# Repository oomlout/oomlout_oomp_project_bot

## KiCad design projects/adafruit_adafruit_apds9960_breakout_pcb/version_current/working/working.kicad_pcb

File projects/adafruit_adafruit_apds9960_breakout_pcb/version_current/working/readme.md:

# Adafruit-APDS9960-Breakout-PCB by adafruit  
This is a harvested standardized copy of a project from github.  
The original project can be found at:  
https://github.com/adafruit/Adafruit-APDS9960-Breakout-PCB  
Please consult that link for additional, details, files, and license information.  
Note: It was auto harvested and if the original repo had more than one board file or anything out of the ordinary the files here are likely not representative.

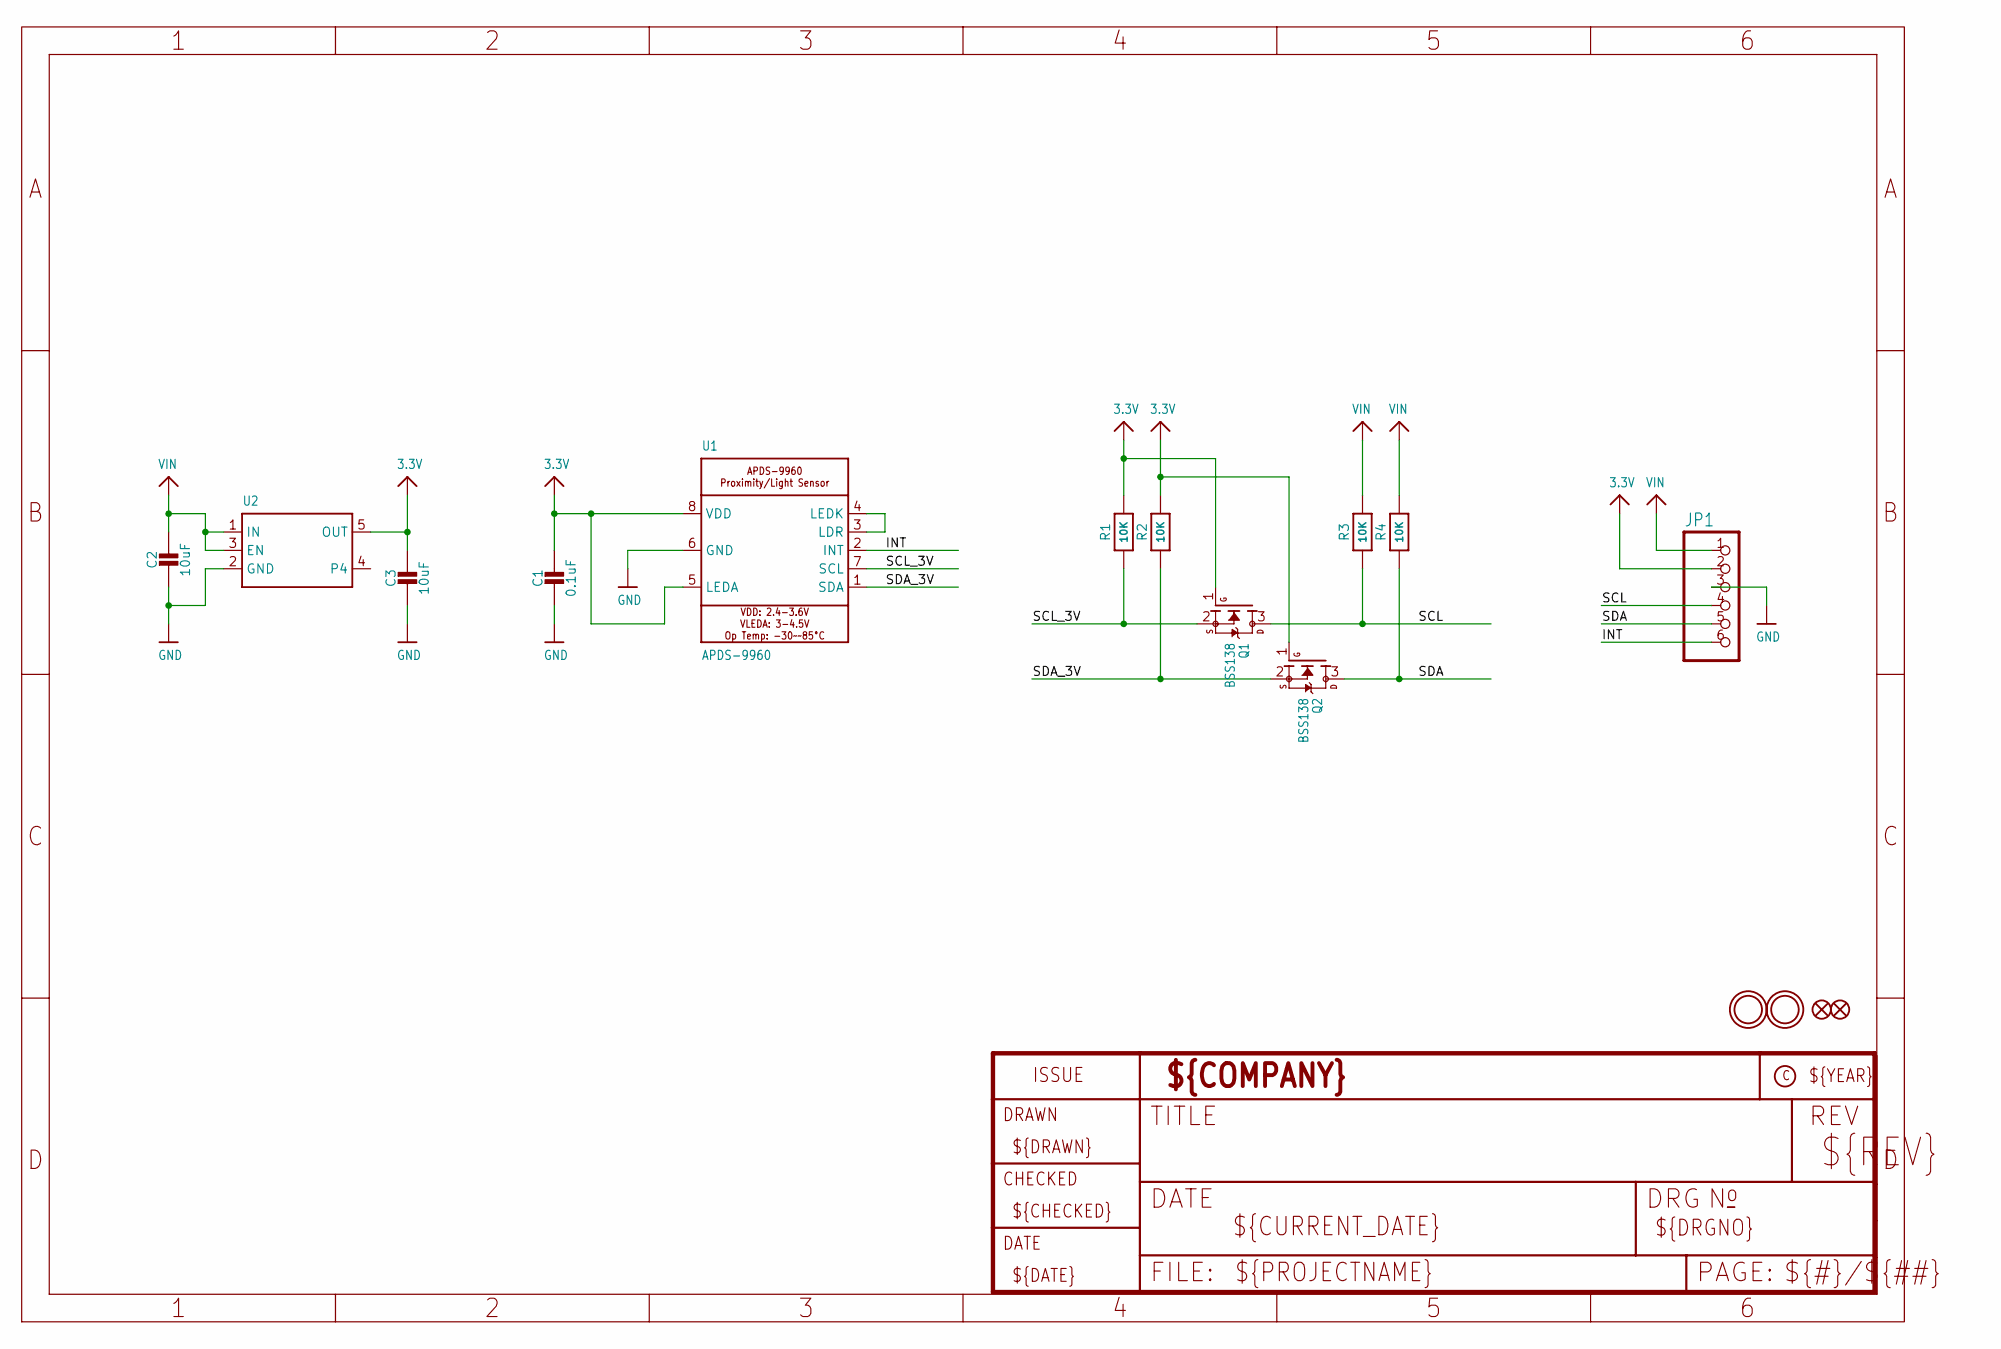
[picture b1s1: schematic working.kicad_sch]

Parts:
C1: 0.1uF; 0805-NO
C2, C3: 10uF; 0805-NO
FID1, FID2: FIDUCIAL_1MM
JP1: HEADER-1X676MIL; 1X06_ROUND_76
Q1, Q2: BSS138; SOT23-WIDE
R1, R2, R3, R4: 10K; 0805-NO
U1: APDS-9960
U2: VREG_SOT23-5; SOT23-5
U$1, U$2: MOUNTINGHOLE2.5; MOUNTINGHOLE_2.5_PLATED

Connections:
3.3V: C1.1, C3.1, JP1.2, Q1.1 (G), Q2.1 (G), R1.2, R2.2, U1.5 (LEDA), U1.8 (VDD), U2.5 (OUT)
GND: C1.2, C2.2, C3.2, JP1.3, U1.6 (GND), U2.2 (GND)
INT: JP1.6, U1.2 (INT)
unnamed: U1.3 (LDR), U1.4 (LEDK)
SCL: JP1.4, Q1.3 (D), R3.1
SCL_3V: Q1.2 (S), R1.1, U1.7 (SCL)
SDA: JP1.5, Q2.3 (D), R4.1
SDA_3V: Q2.2 (S), R2.1, U1.1 (SDA)
VIN: C2.1, JP1.1, R3.2, R4.2, U2.1 (IN), U2.3 (EN)

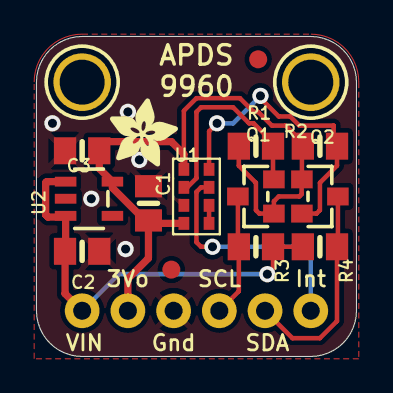
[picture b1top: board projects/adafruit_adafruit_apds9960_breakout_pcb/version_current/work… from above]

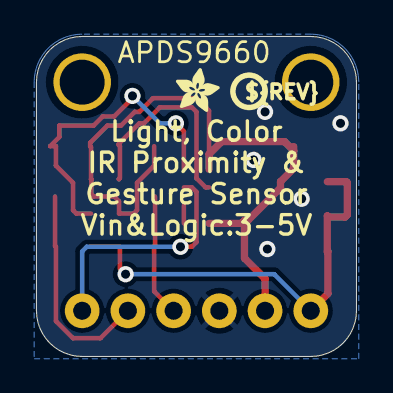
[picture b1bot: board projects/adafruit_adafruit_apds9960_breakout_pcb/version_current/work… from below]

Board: 2 copper layers, 17.8 x 17.8 mm, 19 parts (2 on the bottom side), 9 nets.

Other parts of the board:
U$17: PCBFEAT-REV-040
U$18: ADAFRUIT_2.5MM
U$19: ADAFRUIT_3.5MM

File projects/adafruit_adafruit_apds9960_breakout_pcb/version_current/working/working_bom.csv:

Row,Description,Part,References,Value,Footprint,Quantity Per PCB,Status,Datasheet
1,,CAP_CERAMIC0805-NOOUTLINE,C1,0.1uF,0805-NO,1, ,
2,,CAP_CERAMIC0805-NOOUTLINE,C2 C3,10uF,0805-NO,2, ,
3,,HEADER-1X676MIL,JP1,HEADER-1X676MIL,1X06_ROUND_76,1, ,
4,,MOSFET-NWIDE,Q1 Q2,BSS138,SOT23-WIDE,2, ,
5,,RESISTOR0805_NOOUTLINE,R1 R2 R3 R4,10K,0805-NO,4, ,
6,,APDS-9960,U1,APDS-9960,APDS-9960,1, ,
7,,VREG_SOT23-5,U2,VREG_SOT23-5,SOT23-5,1, ,





Project info:
Schematic:,working
Variant:,default
Revision:,
Date:,2023-08-02_17-08-32
KiCad Version:,7.0.6-7.0.6~ubuntu22.04.1
Statistics:
Component Groups:,7
Component Count:,12 (0 SMD/ 0 THT)
Fitted Components:,12 (0 SMD/ 0 THT)
Number of PCBs:,1
Total Components:,12

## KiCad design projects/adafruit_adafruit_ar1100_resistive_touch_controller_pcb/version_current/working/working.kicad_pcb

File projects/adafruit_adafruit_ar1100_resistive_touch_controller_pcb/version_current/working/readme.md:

# Adafruit-AR1100-Resistive-Touch-Controller-PCB by adafruit  
This is a harvested standardized copy of a project from github.  
The original project can be found at:  
https://github.com/adafruit/Adafruit-AR1100-Resistive-Touch-Controller-PCB  
Please consult that link for additional, details, files, and license information.  
Note: It was auto harvested and if the original repo had more than one board file or anything out of the ordinary the files here are likely not representative.

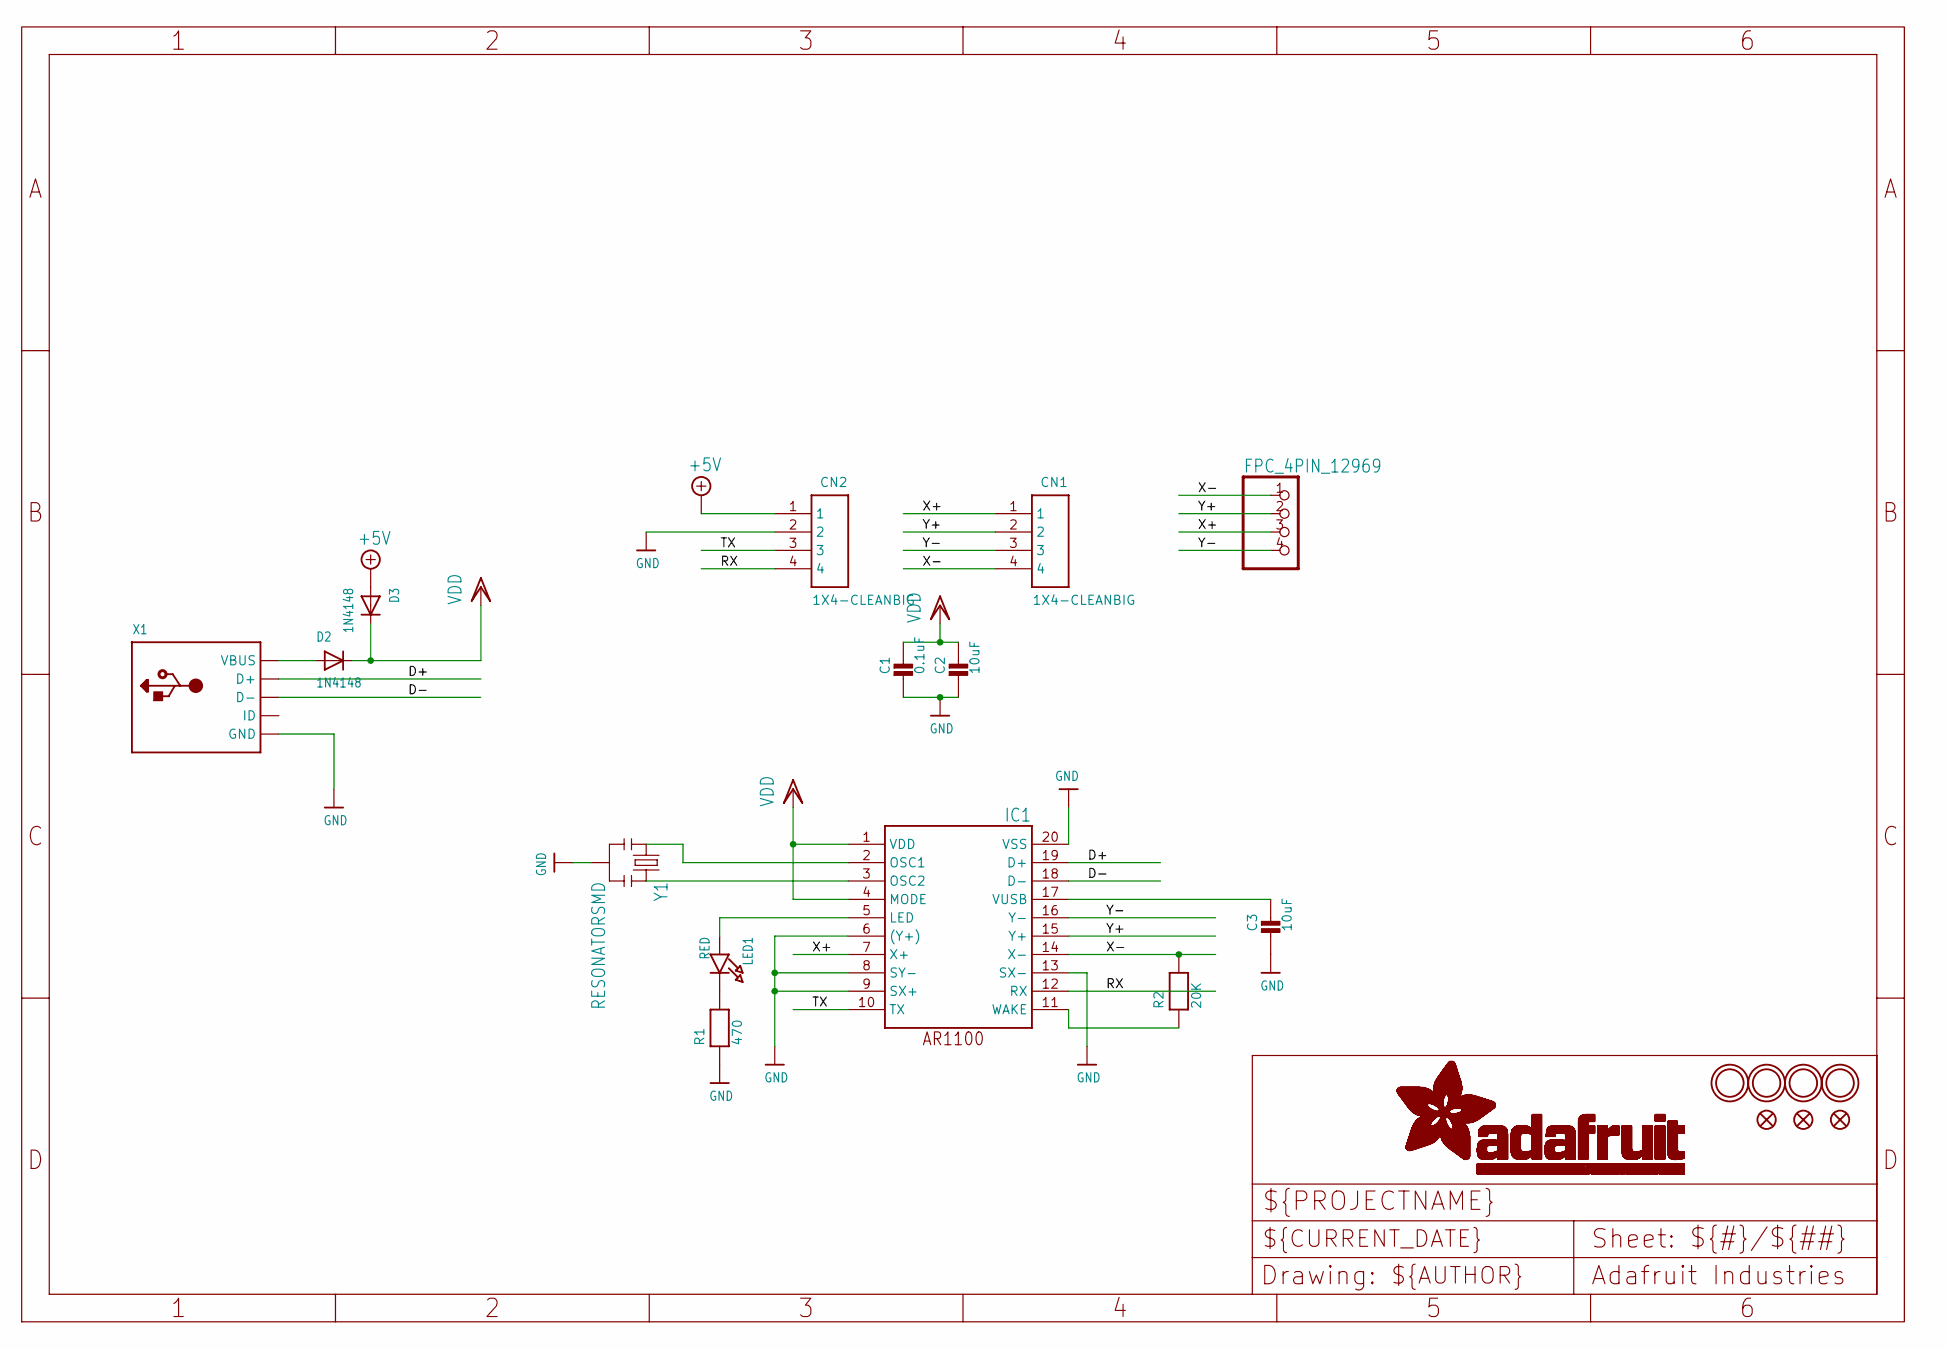
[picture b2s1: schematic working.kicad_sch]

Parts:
C1: 0.1uF; 0805-NO
C2, C3: 10uF; 0805-NO
CN1, CN2: 1X4-CLEANBIG; 1X04-CLEANBIG
D2, D3: 1N4148; SOD-323F
FID1, FID2, FID3: FIDUCIAL""; FIDUCIAL_1MM
IC1: AR1100_SSOP; TSSOP20-5.3MMBODY
LED1: RED; CHIPLED_0805_NOOUTLINE
R1: 470; 0805-NO
R2: 20K; 0805-NO
U$2, U$4, U$5, U$6: MOUNTINGHOLE2.5; MOUNTINGHOLE_2.5_PLATED
U$7: FPC_4PIN_12969; FPC_CONN_1MM_DUAL_4P
X1: USBMINIB; USB-MINIB
Y1: RESONATORSMD; RESONATOR-SMD

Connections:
+5V: CN2.1, D3.A
D+: IC1.19 (D+), X1.D+
D-: IC1.18 (D-), X1.D-
GND: C1.2, C2.2, C3.2, CN2.2, IC1.6 ((Y+)), IC1.8 (SY-), IC1.9 (SX+), IC1.13 (SX-), IC1.20 (VSS), R1.1, X1.GND, X1.GND1 (GND), X1.GND2 (GND), X1.GND3 (GND), X1.GND4 (GND), Y1.2
unnamed: D2.A, X1.VBUS
unnamed: IC1.5 (LED), LED1.A
unnamed: LED1.C, R1.2
unnamed: C3.1, IC1.17 (VUSB)
unnamed: IC1.11 (WAKE), R2.1
unnamed: IC1.3 (OSC2), Y1.3
unnamed: IC1.2 (OSC1), Y1.1
RX: CN2.4, IC1.12 (RX)
TX: CN2.3, IC1.10 (TX)
VDD: C1.1, C2.1, D2.C, D3.C, IC1.1 (VDD), IC1.4 (MODE)
X+: CN1.1, IC1.7 (X+), U$7.3 (2)
X-: CN1.4, IC1.14 (X-), R2.2, U$7.1 (4)
Y+: CN1.2, IC1.15 (Y+), U$7.2 (3)
Y-: CN1.3, IC1.16 (Y-), U$7.4 (1)

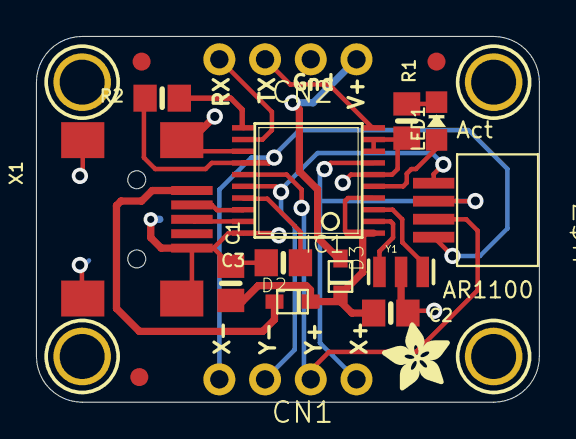
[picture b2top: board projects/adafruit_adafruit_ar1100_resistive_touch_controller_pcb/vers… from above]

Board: 2 copper layers, 27.9 x 20.3 mm, 23 parts (1 on the bottom side), 18 nets.

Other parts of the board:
U$14: ADAFRUIT_3.5MM
U$17: ADAFRUIT_TEXT_20MM

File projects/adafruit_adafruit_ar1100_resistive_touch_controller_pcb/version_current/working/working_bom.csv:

Row,Description,Part,References,Value,Footprint,Quantity Per PCB,Status,Datasheet,BOM
1,,CAP_CERAMIC0805-NOOUTLINE,C1,0.1uF,0805-NO,1, ,,
2,,CAP_CERAMIC0805-NOOUTLINE,C2 C3,10uF,0805-NO,2, ,,
3,,1X4-CLEANBIG,CN1 CN2,1X4-CLEANBIG,1X04-CLEANBIG,2, ,,
4,,DIODESOD-323F,D2 D3,1N4148,SOD-323F,2, ,,
5,,AR1100_SSOP,IC1,AR1100_SSOP,TSSOP20-5.3MMBODY,1, ,,
6,,LED0805_NOOUTLINE,LED1,RED,CHIPLED_0805_NOOUTLINE,1, ,,
7,,RESISTOR0805_NOOUTLINE,R1,470,0805-NO,1, ,,
8,,RESISTOR0805_NOOUTLINE,R2,20K,0805-NO,1, ,,
9,,FPC_4PIN_12969,U$7,FPC_4PIN_12969,FPC_CONN_1MM_DUAL_4P,1, ,,
10,,USBMINIB,X1,USBMINIB,USB-MINIB,1, ,,
11,,RESONATORSMD,Y1,RESONATORSMD,RESONATOR-SMD,1, ,,





Project info:
Schematic:,working
Variant:,default
Revision:,
Date:,2023-08-02_17-08-32
KiCad Version:,7.0.6-7.0.6~ubuntu22.04.1
Statistics:
Component Groups:,11
Component Count:,14 (0 SMD/ 0 THT)
Fitted Components:,14 (0 SMD/ 0 THT)
Number of PCBs:,1
Total Components:,14

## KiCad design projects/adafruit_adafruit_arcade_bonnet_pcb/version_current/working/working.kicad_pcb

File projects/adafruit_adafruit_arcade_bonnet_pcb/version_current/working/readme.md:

# OOMP Project  
## Adafruit-Arcade-Bonnet-PCB  by adafruit  
  
oomp key: oomp_projects_flat_adafruit_adafruit_arcade_bonnet_pcb  
(snippet of original readme)  
  
-- Adafruit Arcade Bonnet PCB  
  
<a href="http://www.adafruit.com/products/3422"><br/>  
Click here to purchase one from the Adafruit shop</a>  
  
PCB files for the Adafruit Arcade Bonnet. Format is EagleCAD schematic and board layout  
* http://www.adafruit.com/product/3422  
  
--- Description  
  
Playing retro games is easy on a Raspberry Pi - and that pocket-sized computer is pretty good at it too! All you need is a little help to connect buttons and a joystick up and you can custom design your own arcade console, desktop or stand-up machine, even just a simple controller box. It makes for a fun weekend project that will last all year.  
  
This Adafruit Arcade Bonnet is designed to make small emulator projects a little easier to build. Here's what you can look forward to!  
  
* It is the same size as a Pi Zero, so for really compact builds, this is super small. You can also use it with a Pi 2, 3, B+ or any 2x20 connector Pi.  
* It has JST sockets so you can plug in six arcade buttons easily using our quick connects.  
* Header breakouts for use with both clicky-type switched joysticks and...  
* Header breakout and converter for using analog-type joysticks or thumbsticks with potentiometers inside.  
* A 3W digital speaker output that can drive 4-8 ohm speakers for when using with a TV output, audio-less HDMI display or PiTFT. Works even when the Pi doesn't have a headphone jack!  
* Switches are all managed with an I2C-GPIO converter with interrupt ou  
  full source readme at [readme_src.md](readme_src.md)  
  
source repo at: [https://github.com/adafruit/Adafruit-Arcade-Bonnet-PCB](https://github.com/adafruit/Adafruit-Arcade-Bonnet-PCB)  
## Board  

## Schematic  

[schematic pdf](working_schematic.pdf)  
## Images

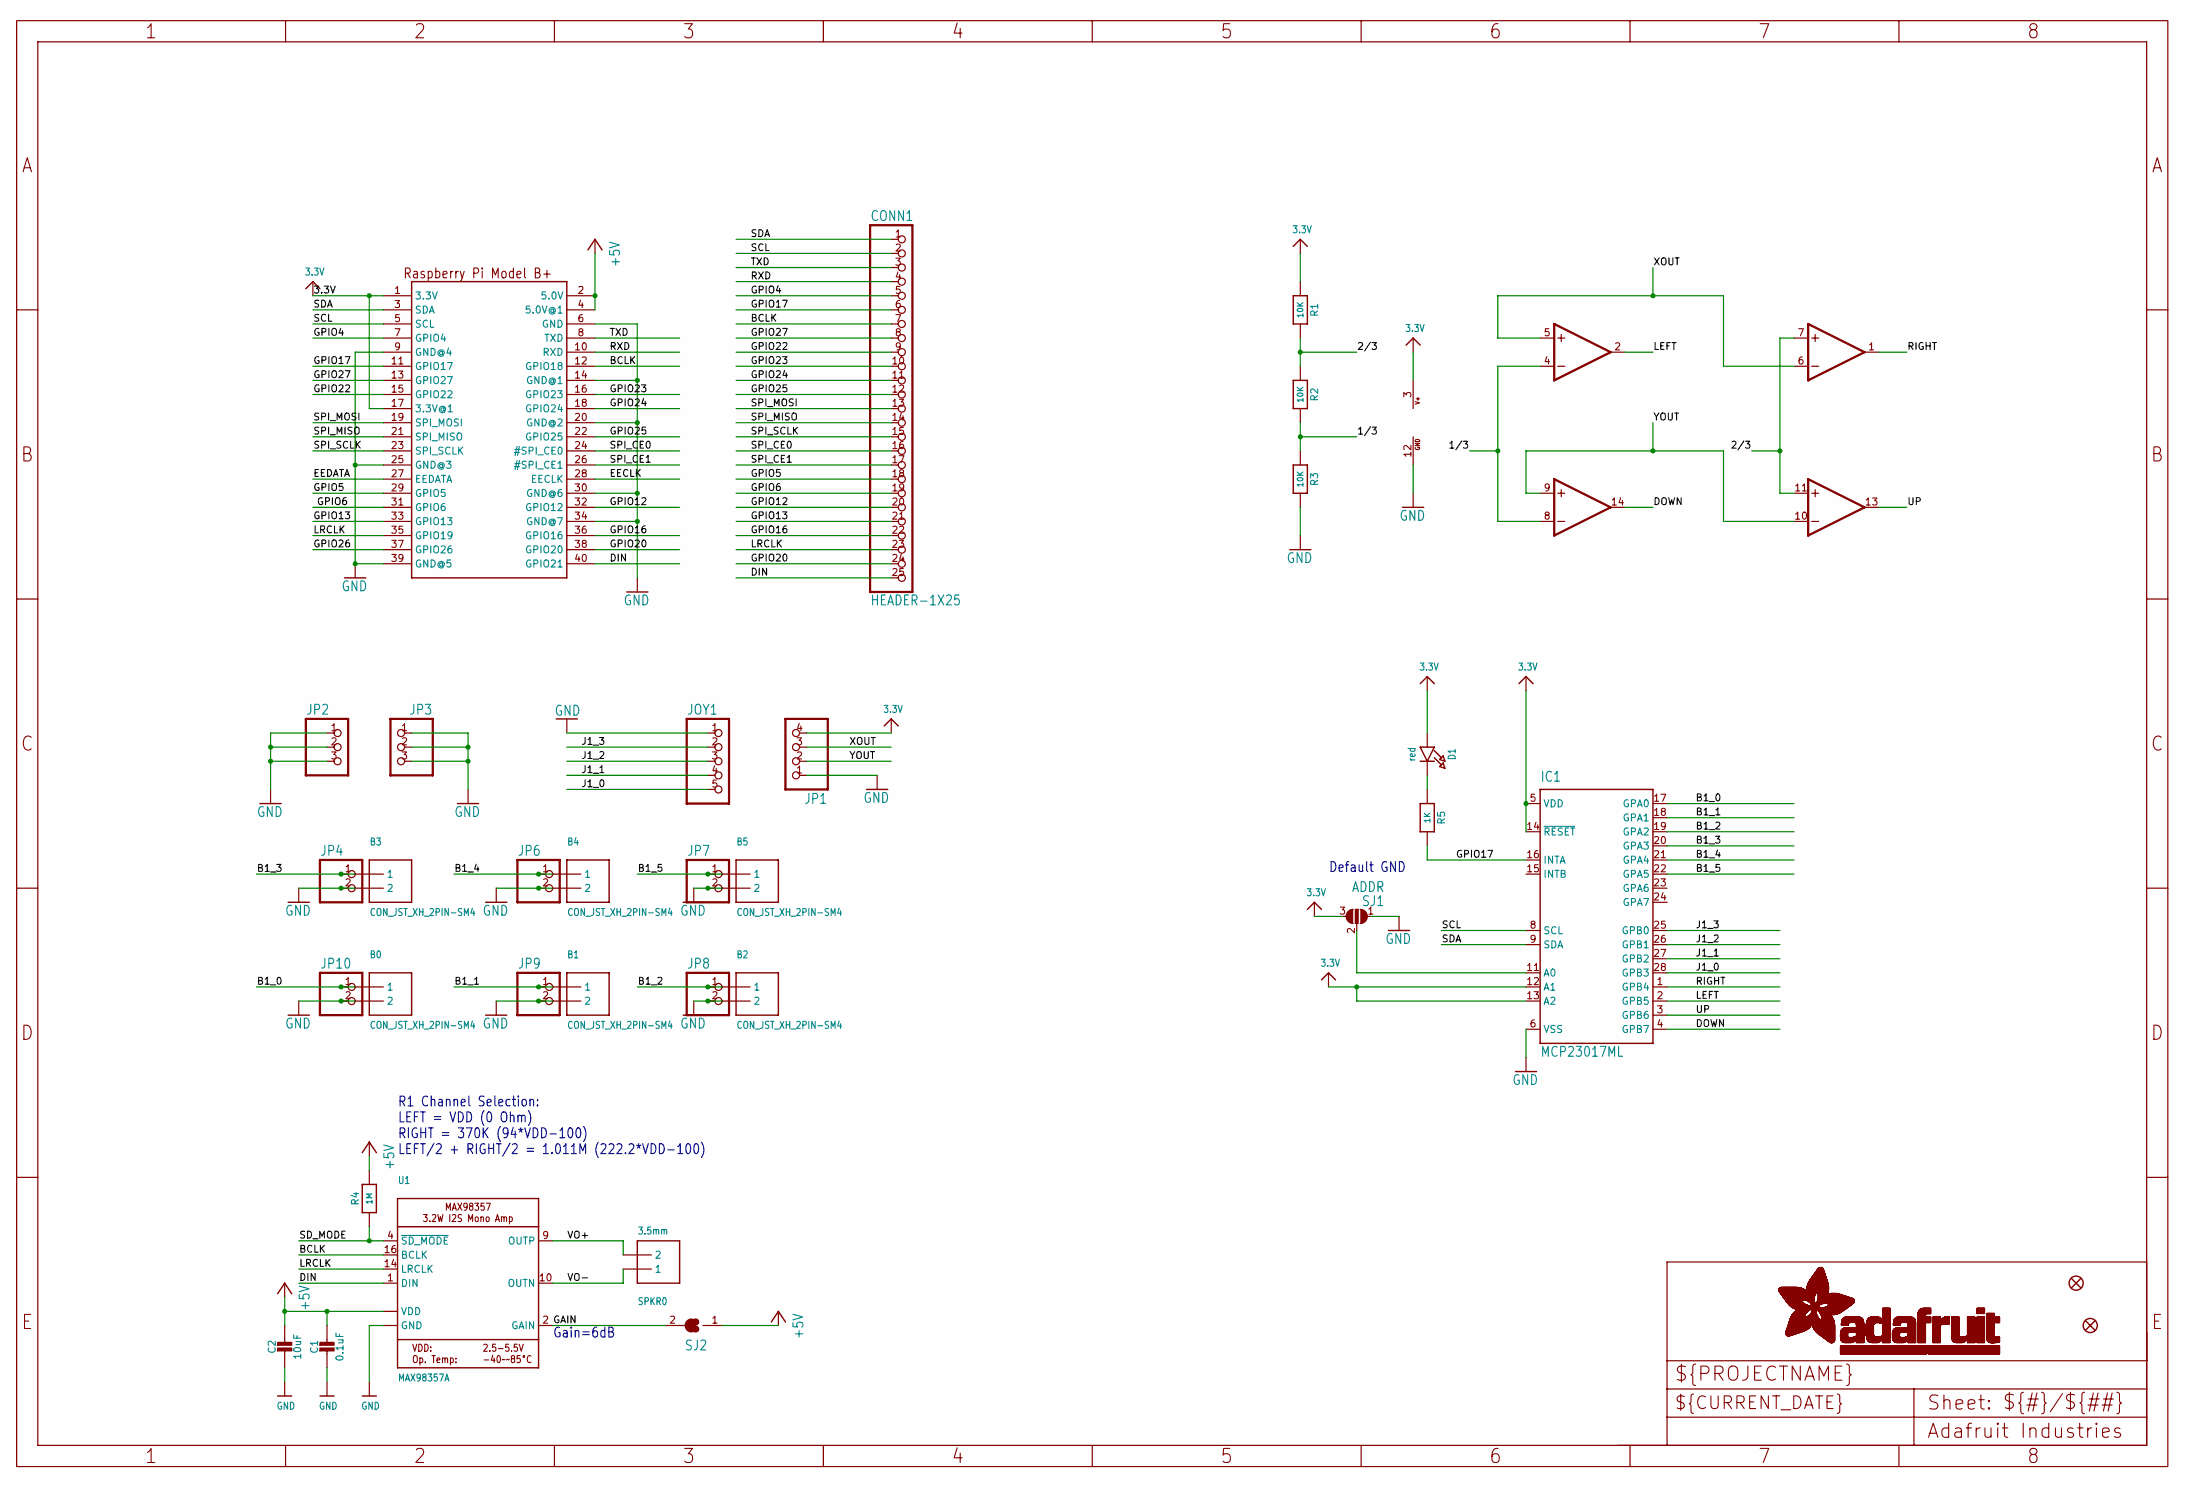
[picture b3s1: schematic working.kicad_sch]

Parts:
B0, B1, B2, B3, B4, B5: CON_JST_XH_2PIN-SM4; JST-XH-2-SM4
C1: 0.1uF; 0603-NO
C2: 10uF; 0805-NO
CONN1: HEADER-1X25; 1X25_ROUND_70MIL
D1: red; CHIPLED_0805_NOOUTLINE
FID2, FID3: FIDUCIAL""; FIDUCIAL_1MM
IC1: MCP23017ML; QFN28-ML_6X6MM; MPN MCP23017-E/SS
IC2: LM339P; TSSOP14
JOY1: HEADER-1X5; 1X05_OVAL
JP1: HEADER-1X4; 1X04_OVAL
JP2, JP3: HEADER-1X3ROUND; 1X03_ROUND
JP4, JP6, JP7, JP8, JP9, JP10: HEADER-1X2; 1X02_OVAL
R1: 10K; 0805_10MGAP
R2, R3: 10K; 0805-NO
R4: 1M; 0603-NO
R5: 1K; 0603-NO
RPI1: RASPBERRYPI_BPLUS_PHAT; PI_BONNET
SJ1: ADDR; SOLDERJUMPER_2WAY_OPEN_NOPASTE
SJ2: SOLDERJUMPERCLOSED; SOLDERJUMPER_CLOSEDWIRE
SPKR0: 3.5mm; TERMBLOCK_1X2-3.5MM
U1: MAX98357A; QFN16_3MM

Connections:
1/3: IC2.4 (-IN), IC2.8 (-IN), R2.2, R3.1
2/3: IC2.7 (+IN), IC2.11 (+IN), R1.2, R2.1
3.3V: D1.A, IC1.5 (VDD), IC1.12 (A1), IC1.13 (A2), IC1.14 (~RESET), IC2.3 (V+), JP1.4, R1.1, RPI1.1 (3.3V), RPI1.17 (3.3V@1), SJ1.3
+5V: C1.1, C2.1, R4.2, RPI1.2 (5.0V), RPI1.4 (5.0V@1), SJ2.1, U1.7 (VDD), U1.8 (VDD)
B1_0: B0.1, IC1.17 (GPA0), JP10.1
B1_1: B1.1, IC1.18 (GPA1), JP9.1
B1_2: B2.1, IC1.19 (GPA2), JP8.1
B1_3: B3.1, IC1.20 (GPA3), JP4.1
B1_4: B4.1, IC1.21 (GPA4), JP6.1
B1_5: B5.1, IC1.22 (GPA5), JP7.1
BCLK: CONN1.7, RPI1.12 (GPIO18), U1.16 (BCLK)
DIN: CONN1.25, RPI1.40 (GPIO21), U1.1 (DIN)
DOWN: IC1.4 (GPB7), IC2.14 (OUT)
EECLK: RPI1.28 (EECLK)
EEDATA: RPI1.27 (EEDATA)
GAIN: SJ2.2, U1.2 (GAIN)
GND: B0.2, B1.2, B2.2, B3.2, B4.2, B5.2, C1.2, C2.2, IC1.6 (VSS), IC2.12 (GND), JOY1.1, JP1.1, JP2.1, JP2.2, JP2.3, JP3.1, JP3.2, JP3.3, JP4.2, JP6.2, JP7.2, JP8.2, JP9.2, JP10.2, R3.2, RPI1.6 (GND), RPI1.9 (GND@4), RPI1.14 (GND@1), RPI1.20 (GND@2), RPI1.25 (GND@3), RPI1.30 (GND@6), RPI1.34 (GND@7), RPI1.39 (GND@5), SJ1.1, U1.3 (GND), U1.11 (GND), U1.15 (GND), U1.THERMAL (GND)
GPIO4: CONN1.5, RPI1.7 (GPIO4)
GPIO5: CONN1.18, RPI1.29 (GPIO5)
GPIO6: CONN1.19, RPI1.31 (GPIO6)
GPIO12: CONN1.20, RPI1.32 (GPIO12)
GPIO13: CONN1.21, RPI1.33 (GPIO13)
GPIO16: CONN1.22, RPI1.36 (GPIO16)
GPIO17: CONN1.6, IC1.16 (INTA), R5.2, RPI1.11 (GPIO17)
GPIO20: CONN1.24, RPI1.38 (GPIO20)
GPIO22: CONN1.9, RPI1.15 (GPIO22)
GPIO23: CONN1.10, RPI1.16 (GPIO23)
GPIO24: CONN1.11, RPI1.18 (GPIO24)
GPIO25: CONN1.12, RPI1.22 (GPIO25)
GPIO26: RPI1.37 (GPIO26)
GPIO27: CONN1.8, RPI1.13 (GPIO27)
J1_0: IC1.28 (GPB3), JOY1.5
J1_1: IC1.27 (GPB2), JOY1.4
J1_2: IC1.26 (GPB1), JOY1.3
J1_3: IC1.25 (GPB0), JOY1.2
LEFT: IC1.2 (GPB5), IC2.2 (OUT)
LRCLK: CONN1.23, RPI1.35 (GPIO19), U1.14 (LRCLK)
unnamed: IC1.11 (A0), SJ1.2
unnamed: D1.C, R5.1
RIGHT: IC1.1 (GPB4), IC2.1 (OUT)
RXD: CONN1.4, RPI1.10 (RXD)
SCL: CONN1.2, IC1.8 (SCL), RPI1.5 (SCL)
SDA: CONN1.1, IC1.9 (SDA), RPI1.3 (SDA)
SD_MODE: R4.1, U1.4 (~SD_MODE)
SPI_CE0: CONN1.16, RPI1.24 (#SPI_CE0)
SPI_CE1: CONN1.17, RPI1.26 (#SPI_CE1)
SPI_MISO: CONN1.14, RPI1.21 (SPI_MISO)
SPI_MOSI: CONN1.13, RPI1.19 (SPI_MOSI)
SPI_SCLK: CONN1.15, RPI1.23 (SPI_SCLK)
TXD: CONN1.3, RPI1.8 (TXD)
UP: IC1.3 (GPB6), IC2.13 (OUT)
VO+: SPKR0.2, U1.9 (OUTP)
VO-: SPKR0.1, U1.10 (OUTN)
XOUT: IC2.5 (+IN), IC2.6 (-IN), JP1.3
YOUT: IC2.9 (+IN), IC2.10 (-IN), JP1.2

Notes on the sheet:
R1 Channel Selection: LEFT = VDD (0 Ohm) RIGHT = 370K (94*VDD-100) LEFT/2 + RIGHT/2 = 1.011M (222.2*VDD-100)
Default GND
Gain=6dB

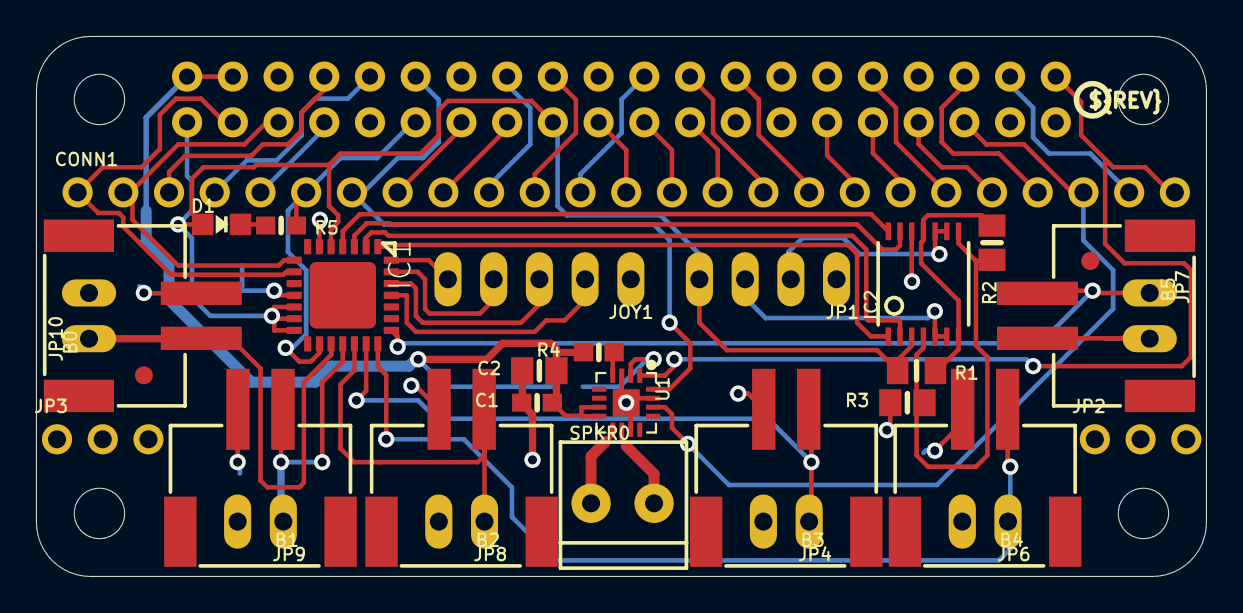
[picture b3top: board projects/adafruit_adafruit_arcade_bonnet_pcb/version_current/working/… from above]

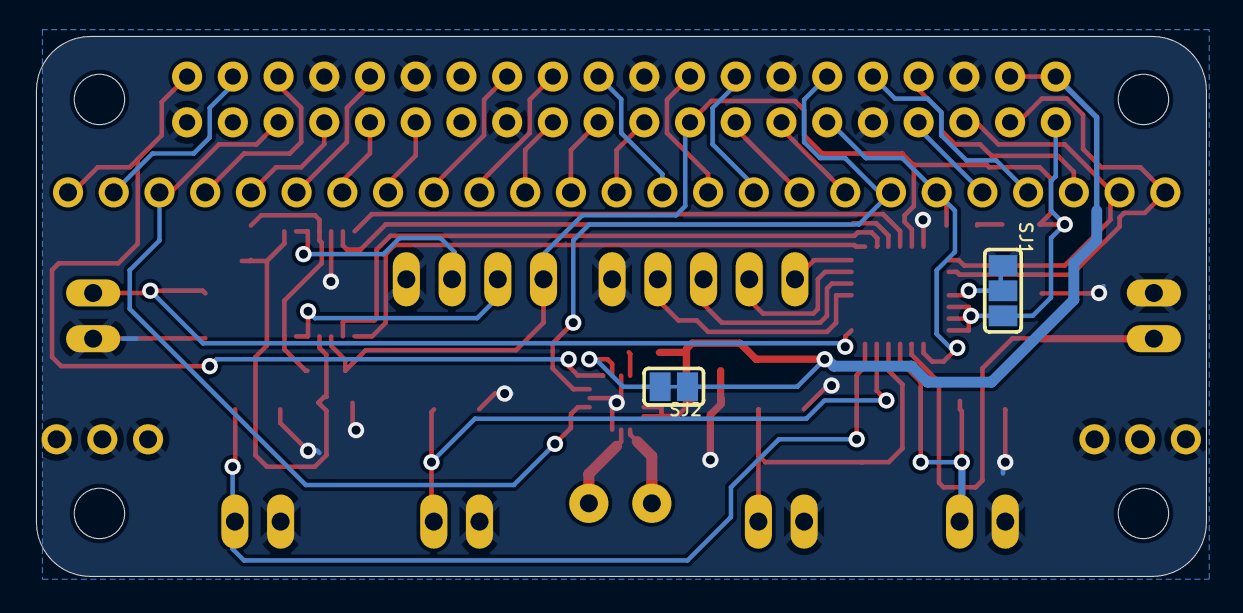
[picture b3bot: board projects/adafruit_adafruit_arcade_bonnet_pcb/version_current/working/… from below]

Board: 2 copper layers, 65.0 x 30.0 mm, 37 parts (3 on the bottom side), 52 nets.

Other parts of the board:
U$11: PCBFEAT-REV-040
U$19: BONNET_ARCADE_REVB_TOP
U$20: BONNET_ARCADE_REVB_BOT

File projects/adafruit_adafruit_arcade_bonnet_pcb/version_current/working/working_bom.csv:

Row,Description,Part,References,Value,Footprint,Quantity Per PCB,Status,Datasheet,MPN,OC_FARNELL,OC_NEWARK
1,,CON_JST_XH_2PIN-SM4,B0 B1 B2 B3 B4 B5,CON_JST_XH_2PIN-SM4,JST-XH-2-SM4,6, ,,,,
2,,CAP_CERAMIC0603_NO,C1,0.1uF,0603-NO,1, ,,,,
3,,CAP_CERAMIC0805-NOOUTLINE,C2,10uF,0805-NO,1, ,,,,
4,,HEADER-1X25,CONN1,HEADER-1X25,1X25_ROUND_70MIL,1, ,,,,
5,,LED0805_NOOUTLINE,D1,red,CHIPLED_0805_NOOUTLINE,1, ,,,,
6,,LM339P,IC2,LM339P,TSSOP14,1, ,,,,
7,,MCP23017ML,IC1,MCP23017ML,QFN28-ML_6X6MM,1, ,,MCP23017-E/SS,1467674,31K2960
8,,HEADER-1X5,JOY1,HEADER-1X5,1X05_OVAL,1, ,,,,
9,,HEADER-1X2,JP4 JP6 JP7 JP8 JP9 JP10,HEADER-1X2,1X02_OVAL,6, ,,,,
10,,HEADER-1X3ROUND,JP2 JP3,HEADER-1X3ROUND,1X03_ROUND,2, ,,,,
11,,HEADER-1X4,JP1,HEADER-1X4,1X04_OVAL,1, ,,,,
12,,RESISTOR_0603_NOOUT,R5,1K,0603-NO,1, ,,,,
13,,RESISTOR0805_10MGAP,R1,10K,0805_10MGAP,1, ,,,,
14,,RESISTOR0805_NOOUTLINE,R2 R3,10K,0805-NO,2, ,,,,
15,,RESISTOR_0603_NOOUT,R4,1M,0603-NO,1, ,,,,
16,,RASPBERRYPI_BPLUS_PHAT,RPI1,RASPBERRYPI_BPLUS_PHAT,PI_BONNET,1, ,,,,
17,,TERMBLOCK_1X2,SPKR0,3.5mm,TERMBLOCK_1X2-3.5MM,1, ,,,,
18,,AUDIOAMP_MAX98357,U1,MAX98357A,QFN16_3MM,1, ,,,,





Project info:
Schematic:,working
Variant:,default
Revision:,
Date:,2023-08-02_17-08-32
KiCad Version:,7.0.6-7.0.6~ubuntu22.04.1
Statistics:
Component Groups:,18
Component Count:,30 (0 SMD/ 0 THT)
Fitted Components:,30 (0 SMD/ 0 THT)
Number of PCBs:,1
Total Components:,30

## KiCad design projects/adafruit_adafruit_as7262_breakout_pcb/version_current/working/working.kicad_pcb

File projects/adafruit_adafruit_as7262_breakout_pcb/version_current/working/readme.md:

# OOMP Project  
## Adafruit-AS7262-Breakout-PCB  by adafruit  
  
oomp key: oomp_projects_flat_adafruit_adafruit_as7262_breakout_pcb  
(snippet of original readme)  
  
-- Adafruit AS7262 Channel Visible Light / Color Sensor Breakout PCB  
  
<a href="http://www.adafruit.com/products/3779"><br/>  
Click here to purchase one from the Adafruit shop</a>  
  
PCB files for AS7262 breakout. Format is EagleCAD schematic and board layout  
  
For more details, check out the product page at  
* https://www.adafruit.com/products/3779  
  
--- Description  
  
Detect trees of green, and red roses too with the new Adafruit AS7262 6-Channel Visible Light / Color Sensor Breakout. This sensor from AMS has 6 integrated visible light sensing channels for red, orange, yellow, green, blue, and violet. These channels can be read via the I2C bus as either raw 16-bit values or calibrated floating-point values. There is also an on-board temperature sensor that can be used to read the temperature of the chip, and a powerful LED flash to reflect light off objects for better color detection.  
  
The 6 channels on the AS7262 are realized by silicon interference filters at 450nm, 500nm, 550nm, 570nm, 600nm, and 650nm. This breakout uses the I2C interface on the chip by default, but a UART interface that accepts AT commands is also selectable.  
  
We've placed the sensor on a PCB for you and included an SPI flash chip pre-programmed with the device firmware, a 3.3V regulator, I2C level shifting, and the recommended LED flash. Both the I2C and UART interfaces are broken out, making this breakout an excellent all-in-one solution for all your color-se  
  full source readme at [readme_src.md](readme_src.md)  
  
source repo at: [https://github.com/adafruit/Adafruit-AS7262-Breakout-PCB](https://github.com/adafruit/Adafruit-AS7262-Breakout-PCB)  
## Board  

## Schematic  

[schematic pdf](working_schematic.pdf)  
## Images

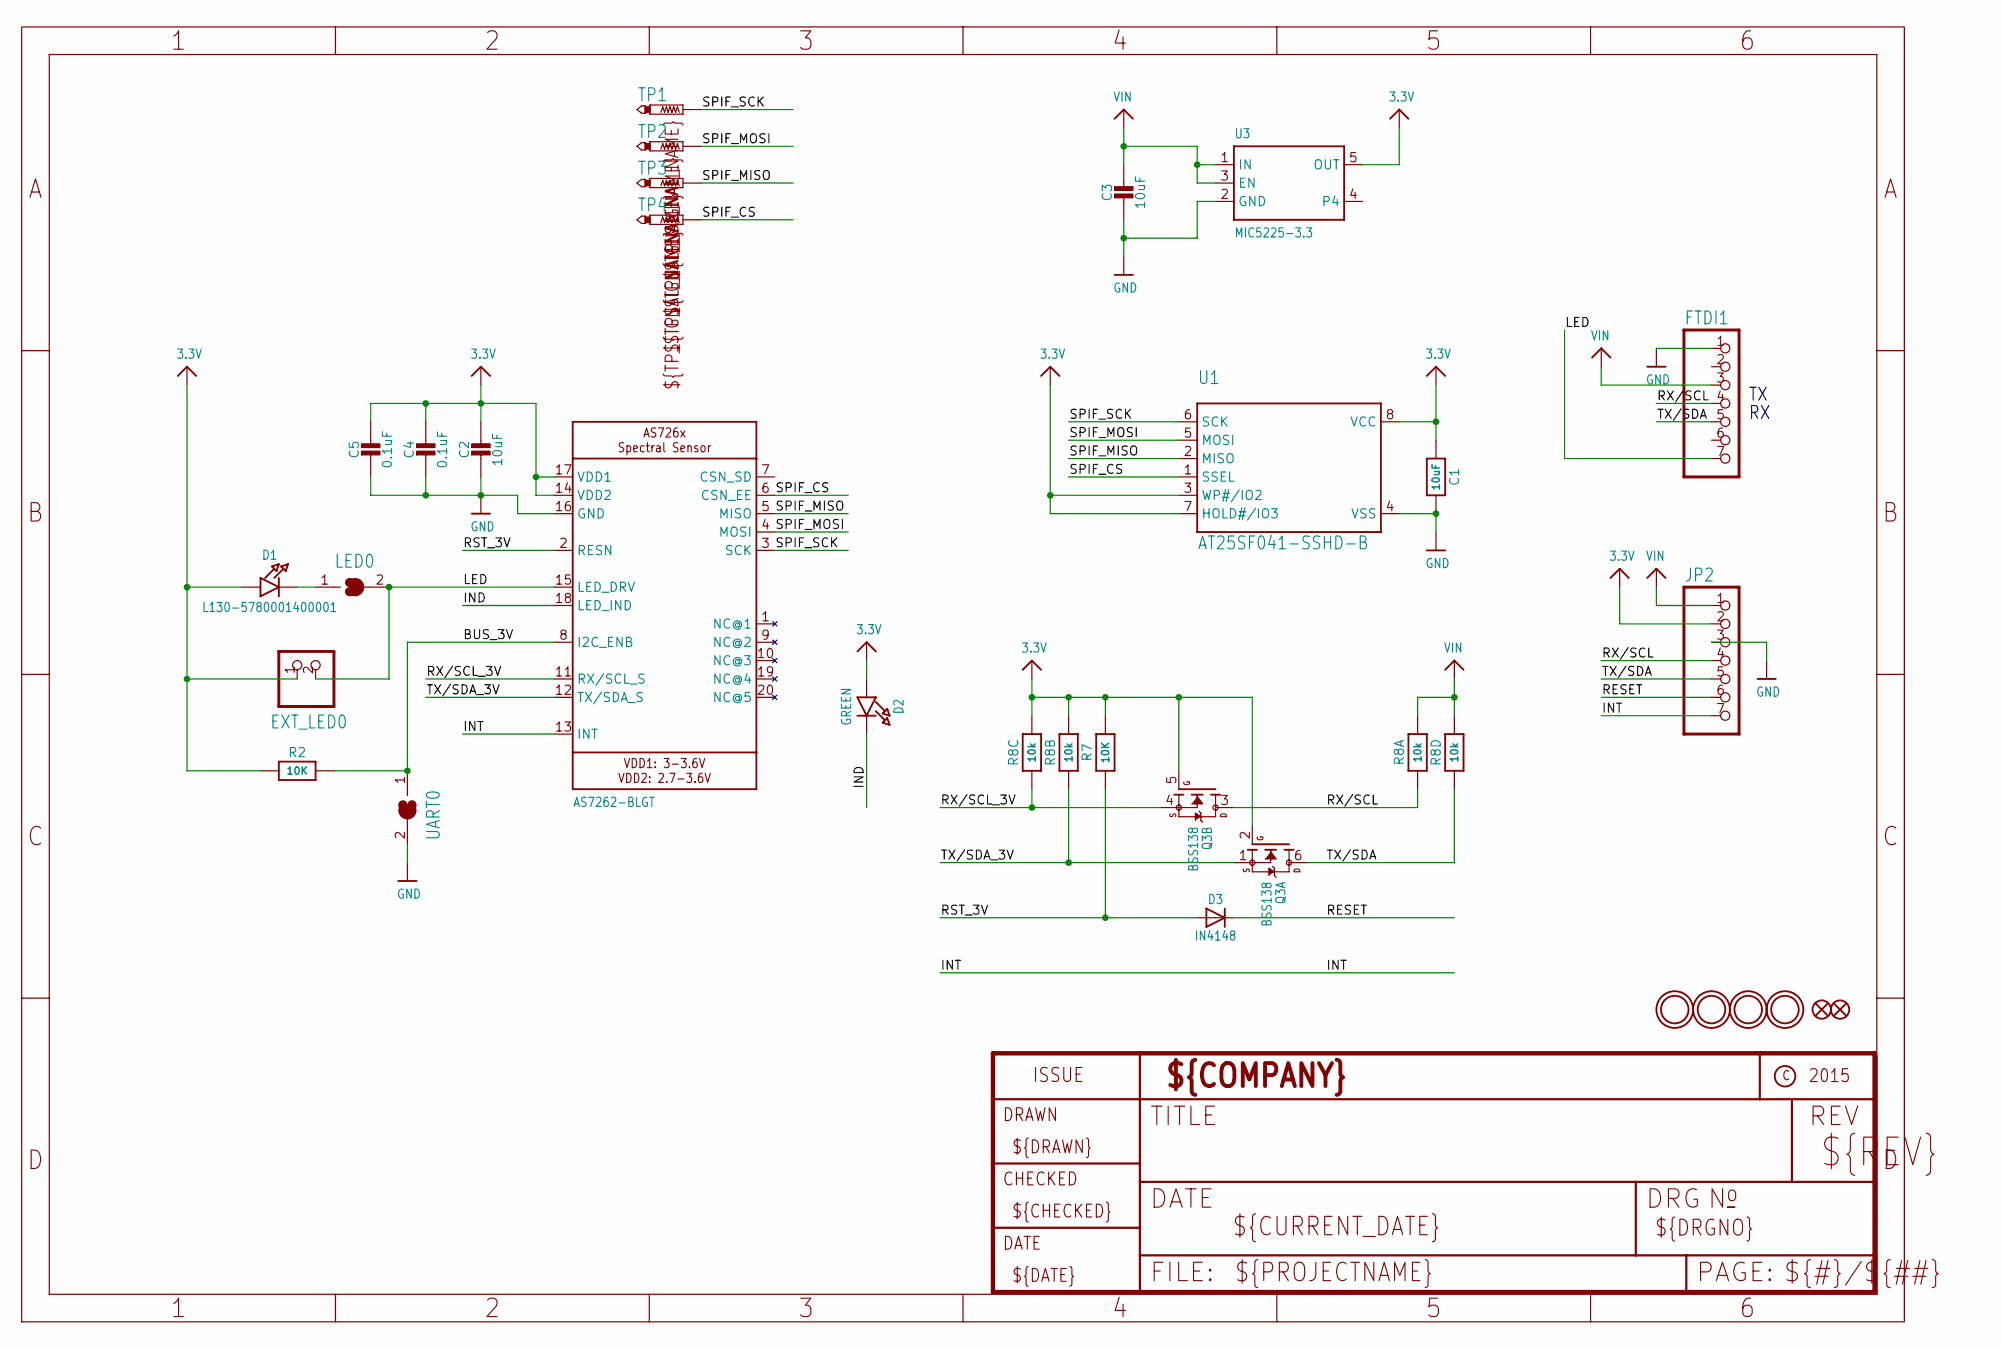
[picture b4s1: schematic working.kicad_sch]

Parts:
C1, C2, C3: 10uF; 0805-NO
C4, C5: 0.1uF; 0603-NO
D1: L130-5780001400001; EVERLIGHT_45-21
D2: GREEN; CHIPLED_0805_NOOUTLINE
D3: IN4148; SOD-323
EXT_LED0: HEADER-1X2ROUND; 1X02_ROUND
FID2, FID3: FIDUCIAL_1MM
FTDI1: HEADER-1X7ROUND; 1X07_ROUND
JP2: HEADER-1X7ROUND; 1X07_ROUND
LED0: SOLDERJUMPERCLOSED; SOLDERJUMPER_CLOSEDWIRE
Q3: BSS138; SOT363
R2: 10K; 0805-NO
R7: 10K; 0603-NO
R8: 10k; RESPACK_4X0603_NO
TP1, TP2, TP3, TP4: PTR1TP15R; TP15R
U1: AT25SF041-SSHD-B; SOIC8_150MIL
U2: AS7262-BLGT; AS726X_LGA20
U3: MIC5225-3.3; SOT23-5
U$2, U$3, U$22, U$23: MOUNTINGHOLE2.5; MOUNTINGHOLE_2.5_PLATED
UART0: SOLDERJUMPER; SOLDERJUMPER_ARROW_NOPASTE

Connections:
3.3V: C1.1, C2.1, C4.1, C5.1, D1.A, D2.A, EXT_LED0.1, JP2.2, Q3.2 (G), Q3.5 (G), R2.1, R7.2, R8.6 (2), R8.7 (2), U1.3 (WP#/IO2), U1.7 (HOLD#/IO3), U1.8 (VCC), U2.14 (VDD2), U2.17 (VDD1), U3.5 (OUT)
BUS_3V: R2.2, U2.8 (I2C_ENB), UART0.1
GND: C1.2, C2.2, C3.2, C4.2, C5.2, FTDI1.1, JP2.3, U1.4 (VSS), U2.16 (GND), U3.2 (GND), UART0.2
IND: D2.C, U2.18 (LED_IND)
INT: JP2.7, U2.13 (INT)
LED: EXT_LED0.2, FTDI1.7, LED0.2, U2.15 (LED_DRV)
unnamed: D1.K (C), LED0.1
RESET: D3.C, JP2.6
RST_3V: D3.A, R7.1, U2.2 (RESN)
RX/SCL: FTDI1.4, JP2.4, Q3.3 (D), R8.1
RX/SCL_3V: Q3.4 (S), R8.3 (1), U2.11 (RX/SCL_S)
SPIF_CS: TP4.TP, U1.1 (SSEL), U2.6 (CSN_EE)
SPIF_MISO: TP3.TP, U1.2 (MISO), U2.5 (MISO)
SPIF_MOSI: TP2.TP, U1.5 (MOSI), U2.4 (MOSI)
SPIF_SCK: TP1.TP, U1.6 (SCK), U2.3 (SCK)
TX/SDA: FTDI1.5, JP2.5, Q3.6 (D), R8.4 (1)
TX/SDA_3V: Q3.1 (S), R8.2 (1), U2.12 (TX/SDA_S)
VIN: C3.1, FTDI1.3, JP2.1, R8.5 (2), R8.8 (2), U3.1 (IN), U3.3 (EN)

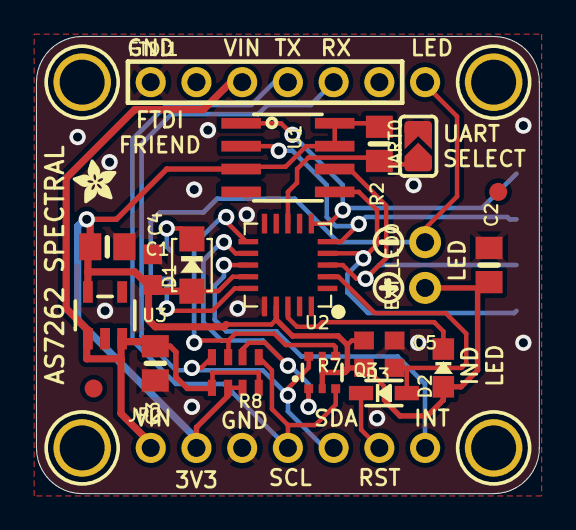
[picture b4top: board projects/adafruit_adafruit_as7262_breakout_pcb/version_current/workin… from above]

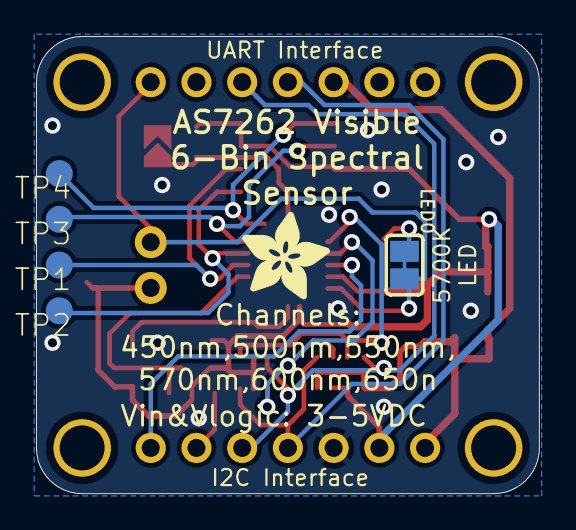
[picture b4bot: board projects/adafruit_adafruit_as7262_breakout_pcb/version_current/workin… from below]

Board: 2 copper layers, 27.9 x 25.4 mm, 34 parts (6 on the bottom side), 18 nets.

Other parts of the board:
U$9: ADAFRUIT_5MM
U$21: ADAFRUIT_2.5MM
U$25: SYMBOL_PLUS
U$26: SYMBOL_MINUS

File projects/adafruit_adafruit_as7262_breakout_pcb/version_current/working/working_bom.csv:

Row,Description,Part,References,Value,Footprint,Quantity Per PCB,Status,Datasheet
1,,CAP_CERAMIC0603_NO,C4 C5,0.1uF,0603-NO,2, ,
2,,RESISTOR0805_NOOUTLINE,C1,10uF,0805-NO,1, ,
3,,CAP_CERAMIC0805-NOOUTLINE,C2 C3,10uF,0805-NO,2, ,
4,,LED0805_NOOUTLINE,D2,GREEN,CHIPLED_0805_NOOUTLINE,1, ,
5,,DIODESOD-323,D3,IN4148,SOD-323,1, ,
6,,LEDEV45-21,D1,L130-5780001400001,EVERLIGHT_45-21,1, ,
7,,HEADER-1X2ROUND,EXT_LED0,HEADER-1X2ROUND,1X02_ROUND,1, ,
8,,HEADER-1X7ROUND,FTDI1 JP2,HEADER-1X7ROUND,1X07_ROUND,2, ,
9,,MOSFET-N_DUAL,Q3,BSS138,SOT363,1, ,
10,,RESISTOR0805_NOOUTLINE,R2,10K,0805-NO,1, ,
11,,microbuilder_09_Nov_2015_RESISTOR_0603_NOOUT,R7,10K,0603-NO,1, ,
12,,RESISTOR_4PACK_NO,R8,10k,RESPACK_4X0603_NO,1, ,
13,,AS726X_SPECTRAL,U2,AS7262-BLGT,AS726X_LGA20,1, ,
14,,SPIFLASH_SOIC8,U1,AT25SF041-SSHD-B,SOIC8_150MIL,1, ,
15,,VREG_SOT23-5,U3,MIC5225-3.3,SOT23-5,1, ,





Project info:
Schematic:,working
Variant:,default
Revision:,
Date:,2023-08-02_17-08-32
KiCad Version:,7.0.6-7.0.6~ubuntu22.04.1
Statistics:
Component Groups:,15
Component Count:,18 (0 SMD/ 0 THT)
Fitted Components:,18 (0 SMD/ 0 THT)
Number of PCBs:,1
Total Components:,18
